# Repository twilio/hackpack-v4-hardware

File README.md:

# Hackpack v4 Hardware Collateral
This repo contains all of the hardware collateral you need to create a device functionally equivalent to the [Hackpack v4](https://hackpack.cc/) from [Twilio's SIGNAL 2018](https://signal.twilio.com/) Conference.

See also our [blog post](https://www.twilio.com/blog/open-source-hardware-badge-hackpack-v4) announcing this repository.

## Hardware Collateral

Everything you need to build a badge PCB can be found in the `KiCad` folder. The Hackpack v4 was designed using KiCad major version 5. [Download a copy here](http://kicad-pcb.org/download/).

You'll also need to purchase a Raspberry Pi Zero W and a 8GB or larger MicroSD card to use the board.

### Don't want to use KiCad?

You can find pre-generated Gerbers in the `KiCad/Gerbers` directory. Use them at your PCB house of choice to manufacture a board.

We've also included the bill of materials and schematic in generic formats.

## Firmware

You can find firmware either [through our repository](https://github.com/twilio/hackpack-v4-firmware/) (start with a vanilla Raspbian installation) or pre-imaged on the [Hackpack v4](https://hackpack.cc/) site.

## Special Assembly Instructions

The Bill of Materials can be found in the `KiCad` directory. Some parts cannot be found at the normal supply sources and are best sourced from Amazon. 

The SMD Grove header was impossible to find in the US at the time this repo was released. Use a through hole Grove header and bend the pins with pliers for an excellent substitute.

The Amazon ILI9341 screen linked in the special assembly instructions has an inverted touchscreen to the one we used at the show. To fix the touchscreen driver you'll need to set flags:

```
echo "100" > /home/pi/.ili9341_touch.conf
sudo reboot
```

## License

Hardware collateral is licensed under [Solderpads 2.0](http://solderpad.org/licenses/SHL-2.0/), a hardware wrapper for the Apache 2.0 license. Please find a copy of both licenses in this repository.

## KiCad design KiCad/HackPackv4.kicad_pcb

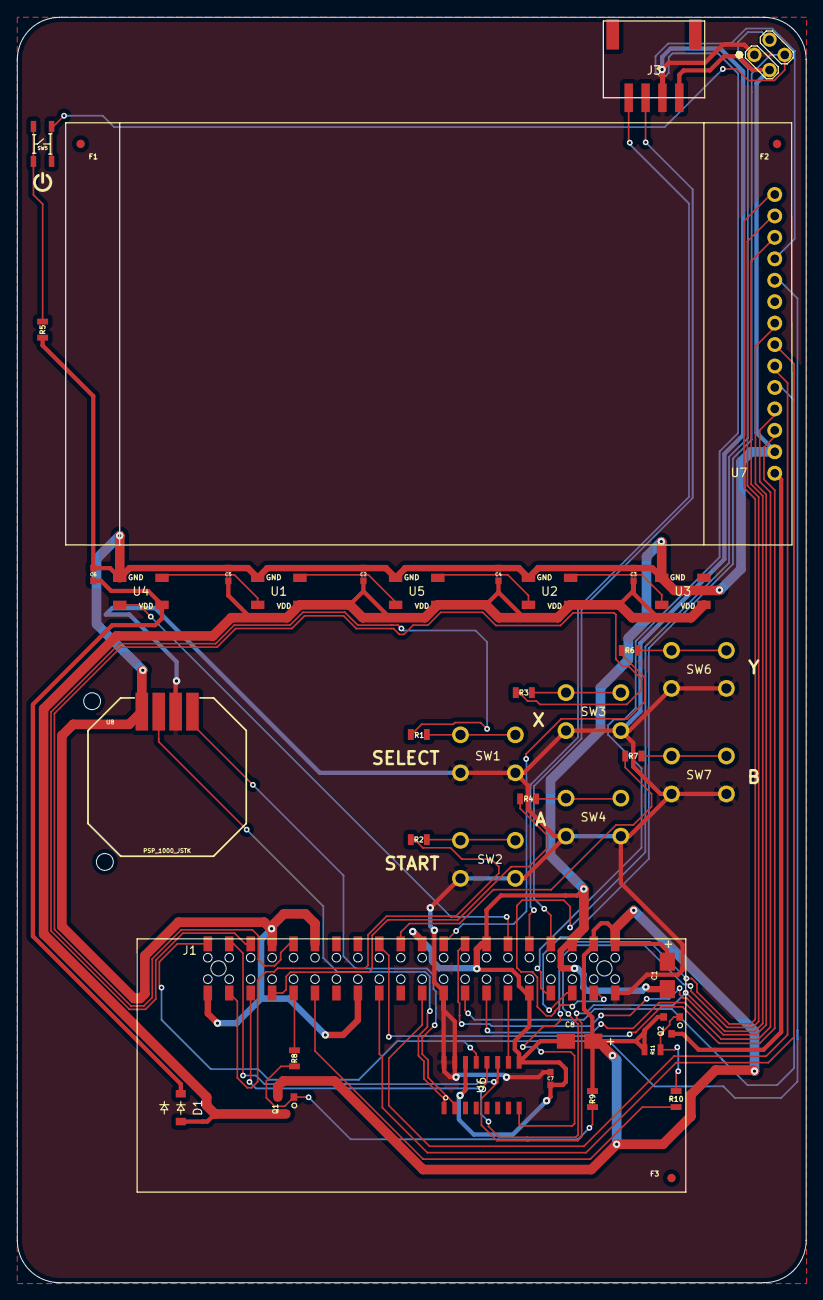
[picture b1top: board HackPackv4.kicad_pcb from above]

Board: 2 copper layers, 93.5 x 149.9 mm, 43 parts (0 on the bottom side), 46 nets.

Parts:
C1, C8: 100uF; CP_Tantalum_Case-B_EIA-3528-21_Wave
C2, C3, C4, C5, C6, C7: .1uF; C_0603
D1: MMSD4148; D_SOD-123
F1, F2, F3: Fiducial_1mm_Dia_2mm_Outer
J1: Raspberry_Pi_Zero_W Header; M20-7812045
J2: Conn_02x02_Odd_Even; Pin_Header_Straight_2x02_Pitch2.54mm
J3: Grove_UART; Grove_Taifeng_1125R-SMT-4P
Q1, Q2: NCE3407A; SOT-23
R1, R2, R3, R4, R6, R7: 1k; R_0805
R5: 330; R_0805
R8, R10: 100; R_0805
R9, R11: 10k; R_0805
SW1: SEL_B; TS-1109_6.2mm_Push
SW2: START_B; TS-1109_6.2mm_Push
SW3: X_B; TS-1109_6.2mm_Push
SW4: A_B; TS-1109_6.2mm_Push
SW5: PWR_B; ALPS_SKRPABE010
SW6: Y_B; TS-1109_6.2mm_Push
SW7: B_B; TS-1109_6.2mm_Push
U1, U2, U3, U4, U5: WS2812B; LED_WS2812B-PLCC4
U6: MCP3008; SOIC-16_3.9x9.9mm_Pitch1.27mm
U7: ILI9341_28_TFT_LCD_TOUCH; ILI9341_TFT_LCD
U8: PSP_1000_JSTK; JOYSTICK-PSP1000

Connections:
+3V3: C7.1, J1.1, J1.17, J2.1, J3.2, SW1.2, SW2.2, SW3.2, SW4.2, SW6.2, SW7.2, U6.15, U6.16, U8.2
+5V: C1.1, C8.1, J1.2, J1.4, Q1.2, Q2.2, R9.1, R11.1
+5V_LCD: Q2.3, U7.1
+5V_LIGHTS: C2.1, C3.1, C4.1, C5.1, D1.2, Q1.3, U1.1, U2.1, U3.1, U5.1
/A_B: J1.33, R4.2
/B_B: J1.22, R7.2
/CS_TOUCH: J1.7, U7.11
/IRQ_TOUCH: U6.8, U7.14
/LCD_BKLT: J1.16, U7.8
/LCD_DC: J1.15, U7.5
/LCD_RESET: J1.13, U7.4
/LED1_PWR: C6.1, D1.1, U4.1
/LED_DATA: J1.12, U4.4
/PWR_ON_OFF: J1.5, J2.4, SW5.2
/Rx: J1.10, J3.4
/SDA: J1.3, J2.2
/SELECT_B: J1.36, R1.2
/SPI0_CE0: J1.24, U7.3
/SPI0_MOSI: J1.19, U7.6
/SPI0_SCK: J1.23, U7.7
/SPI1_CE1: J1.11, U6.10
/SPI1_MISO: J1.35, U6.12, U7.13
/SPI1_MOSI: J1.38, U6.11, U7.12
/SPI1_SCK: J1.40, U6.13, U7.10
/START_B: J1.37, R2.2
/Tx: J1.8, J3.3
/X_B: J1.32, R3.2
/Y_B: J1.18, R6.2
/~LCD_ON: J1.29, R10.2
/~LED_ON: J1.31, R8.2
GND: C1.2, C2.2, C3.2, C4.2, C5.2, C6.2, C7.2, C8.2, J1.6, J1.9, J1.14, J1.20, J1.25, J1.30, J1.34, J1.39, J2.3, J3.1, R5.2, U1.3, U2.3, U3.3, U4.3, U5.3, U6.9, U6.14, U7.2, U8.4
unnamed: Q1.1, R8.1, R9.2
unnamed: Q2.1, R10.1, R11.2
unnamed: R1.1, SW1.1
unnamed: R2.1, SW2.1
unnamed: R3.1, SW3.1
unnamed: R4.1, SW4.1
unnamed: R5.1, SW5.1
unnamed: R6.1, SW6.1
unnamed: R7.1, SW7.1
unnamed: U1.2, U5.4
unnamed: U1.4, U4.2
unnamed: U2.2, U3.4
unnamed: U2.4, U5.2
unnamed: U6.1, U8.3
unnamed: U6.2, U8.1

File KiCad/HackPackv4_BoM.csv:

Component,Description,Part,References,Value,Footprint,Quantity Per PCB,Datasheet,MFP,MFN,Characteristics,Can_Substitute,Notes,Package
1,CAP CER 0.1UF 50V X7R 0603,C_Small,C2 C3 C4 C5 C6 C7,.1uF,C_0603,6,https://www.mouser.com/datasheet/2/281/murata_03122018_GCM_S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,GCM188R71H104KA57D,MURATA,0603 100nF-50V-10%-X7R,Y,,
2,SMD CAP Tantalum 100uF-10V,CP,C1 C8,100uF,CP_Tantalum_Case-B_EIA-3528-21_Wave,2,https://www.mouser.com/datasheet/2/40/f93-776559.pdf,F931A107KBA,AVX,100uF 10V 20%,Y,2x for Smoothing 5V,
3,SMD Diode Switching 100V-200mA,D,D1,MMSD4148,D_SOD-123,1,https://www.onsemi.com/pub/Collateral/MMSD4148T1-D.PDF,MMSD4148T3G,ON Semiconductor,MUST DROP >= .3 Forward Voltage!! SMD Diode Switching 100V-200mA,N,To drop voltage for the first LED to meet the 70% spec.,
4,NO NOT POPULATE,Conn_02x02_Odd_Even,J2,Conn_02x02_Odd_Even,Pin_Header_Straight_2x02_Pitch2.54mm,1,NONE,DNP,DNP,NO NOT POPULATE,N,NO NOT POPULATE,NO NOT POPULATE
5,Grove UART Header - Solder bent pins onto pads,Conn_01x04_Male,J3,Grove_UART,Grove_Taifeng_1125R-SMT-4P,1,https://www.digikey.com/product-detail/en/seeed-technology-c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,Buy on Digikey and Modify,--,,N,Bend pins & solder sideways,
6,Surface mount low profile header 40 pin 2 row,Raspberry_Pi_Zero_W,J1,Raspberry_Pi_Zero_W,M20-7812045,1,https://cdn.harwin.com/pdfs/M20-781.pdf,HLE-120-02-G-DV-A,Samtec,40 Pin 2x20 2.54mm pitch SMD.,Y,WAIT ON SUBSTITUTE FROM ERIN & TWILIO,
7,MOSFET P-CH 30V 4.3A SOT23,NCE3407A,Q1 Q2,NCE3407A,SOT-23,2,http://aosmd.com/res/data_sheets/AO3407A.pdf,AO3407A,Alpha & Omega Semiconductor,"VGS th < -3, 10+V, 500mA+",Y,"Turn on LEDs, Screen",
8,SMD RES 100R-5%-1/8W,R,R8 R10,100,R_0805,2,http://www.yageo.com/documents/recent/PYu-RC_Group_51_RoHS_L_9.pdf,RC0805JR-07100RL,Yageo,100R 5% 1/8W 0805,Y,MOSFET Gate Input Protection,
9,SMD RES 10K-1%-1/8W;0805,R,R9 R11,10k,R_0805,2,http://www.yageo.com/documents/recent/PYu-RC_Group_51_RoHS_L_9.pdf,RC0805FR-0710KL,Yageo,10K 1% or 5% 1/8W,Y,MOSFET Gate Pullup,
10,SMD RES 1K-5%-1/8W;0805,R_Small,R1 R2 R3 R4 R6 R7,1k,R_0805,6,http://www.yageo.com/documents/recent/PYu-RC_Group_51_RoHS_L_9.pdf,RC0805JR-071KL,Yageo,1K 5% 1/8W,Y,,
11,SMD RES 330R-1%-1/8W;0805,R,R5,330,R_0805,1,http://www.yageo.com/documents/recent/PYu-RC_Group_51_RoHS_L_9.pdf,RC0805FR-07330RL,Yageo,0805 5% or 1% 330R 1/8W,Y,Protection on button/pulldown,
12,DIP Button;SPST;160gf,SW_Push,SW4,A_B,TS-1109_6.2mm_Push,1,https://www.ctscorp.com/wp-content/uploads/222A.pdf,222ADVBA,CTS Electrocomponents,,N,Used for SEL/START/A/B/X/Y Buttons,
13,DIP Button;SPST;160gf,SW_Push,SW7,B_B,TS-1109_6.2mm_Push,1,https://www.ctscorp.com/wp-content/uploads/222A.pdf,222ADVBA,CTS Electrocomponents,,N,Used for SEL/START/A/B/X/Y Buttons,
14,SWITCH TACTILE SPST-NO 0.05A 12V,SW_Push,SW5,PWR_B,ALPS_SKRPABE010,1,https://www.e-switch.com/system/asset/product_line/data_shee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,TL3365AF180QG,E-Switch,SMD 4.2mmx3mm 4 contact SPST Push,N,Power button,
15,DIP Button;SPST;160gf,SW_Push,SW1,SEL_B,TS-1109_6.2mm_Push,1,https://www.ctscorp.com/wp-content/uploads/222A.pdf,222ADVBA,CTS Electrocomponents,,N,Used for SEL/START/A/B/X/Y Buttons,
16,DIP Button;SPST;160gf,SW_Push,SW2,START_B,TS-1109_6.2mm_Push,1,https://www.ctscorp.com/wp-content/uploads/222A.pdf,222ADVBA,CTS Electrocomponents,,N,Used for SEL/START/A/B/X/Y Buttons,
17,DIP Button;SPST;160gf,SW_Push,SW3,X_B,TS-1109_6.2mm_Push,1,https://www.ctscorp.com/wp-content/uploads/222A.pdf,222ADVBA,CTS Electrocomponents,,N,Used for SEL/START/A/B/X/Y Buttons,
18,DIP Button;SPST;160gf,SW_Push,SW6,Y_B,TS-1109_6.2mm_Push,1,https://www.ctscorp.com/wp-content/uploads/222A.pdf,222ADVBA,CTS Electrocomponents,,N,Used for SEL/START/A/B/X/Y Buttons,
19,Screen & touch controller from Alibaba/Amazon,ILI9341_28_TFT_LCD_TOUCH,U7,ILI9341_28_TFT_LCD_TOUCH,ILI9341_TFT_LCD,1,https://www.amazon.com/HiLetgo-240X320-Resolution-Display-IL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,Buy on Amazon,ILI9341,"ILI9341 Resistive Touchscreen 2.8"" TFT LCD",N,Solder directly no header,CUSTOM
20,DAC for Joystick and Touch,MCP3008,U6,MCP3008,SOIC-16_3.9x9.9mm_Pitch1.27mm,1,https://www.mouser.com/datasheet/2/268/21295b-72710.pdf,MCP3008T-I/SL,Microchip Technology,Do not substitute,N,DAC,
21,PSP 1000 Joystick,PSP_1000_JSTK,U8,PSP_1000_JSTK,JOYSTICK-PSP1000,1,https://www.amazon.com/IDS-Joystick-Analog-Replacement-Black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,Buy on Amazon,PSP1000_Joystick,"Analog Resistive Joystick, Can Sub from Other Supplier of PSP 1000 Replacement Joystick",Y,Needs 2 screws,CUSTOM
22,LED RGB 5050 SMD,WS2812B,U1 U2 U3 U4 U5,WS2812B,LED_WS2812B-PLCC4,5,http://www.inolux-corp.com/datasheet/SMDLED/Addressable%20LE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,IN-PI554FCH,Inolux,,N,,
